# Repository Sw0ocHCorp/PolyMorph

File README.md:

# PolyMorph

> **Documentation** — architecture, mathematics and control pipelines: see [`docs/`](docs/README.md).
> Read it with `cd docs && npm install && npm run start` (Node.js ≥ 20). Every commit is described in [`CHANGELOG.md`](CHANGELOG.md).

PolyMorph is an Open Source Robotic Rust ecosystem.
It is composed of:
* Remote Controller
* Companion Software
* Simulation Flight Controller Software using Godot as Physics Engine

For the begining of the project I build my own encoding system for the communication between all the softwares:

The SOF of ALL the Frames is "abcd"

## FEATURE DATA ID
| Data Label                    | Data ID   | Data                                          |
| :-------------:               | :-------: | :-------------:                               |
| Command                       | 0001      | Single value (Arm `0a` DisArm `0f`)           |
| Teleoperation                 | 0002      | Single value (Arm `0a` DisArm `0f`)           |
| GNSS Positioning              | 0003      | Single value (Arm `0a` DisArm `0f`)           |
| Internal Perception           | 0004      | Single value (Arm `0a` DisArm `0f`)           |
| Lidar Scan                    | 0005      | Single value (Arm `0a` DisArm `0f`)           |
| Camera Vision                 | 0006      | Single value (Arm `0a` DisArm `0f`)           |
Thoses are the IDs of a data chunk. 
A Data chunk is a collection of potentials measurement, data, etc... relative to a feature

## Teleoperation Data ID
| Data Label                    | Data ID   | Data                                          |
| :-------------:               | :-------: | :-------------:                               |
| Arming/Disarm                 | 000a      | Single value (Arm `0a` DisArm `0f`)           |
| Joystick                      | 000b      | 1 Value / Axis (2 Joystick, 4 Axis)           |

## GNSS Positioning Data ID
| Data Label                    | Data ID   | Data                                          |
| :-------------:               | :-------: | :-------------:                               |
| GPS Lat/Lon Mesurement        | 0012      | Lat/Lon/                                      |
| GPS Speed Heading Mesurement  | 0013      | Speed()/Heading()                             |
| Lidar Measurements            | 0014      | Specific Frame with the LiDAR data            |

## Internal Perception Data ID
| Data Label                    | Data ID   | Data                                          |
| :-------------:               | :-------: | :-------------:                               |
| Drone Speed Setpoint          | 000c      | 1 Value / Axis (3D Vector)                    |
| Drone Angles Setpoint         | 000d      | For the begining 1 Value                      |
| Servos Angles Setpoint        | 000e      | 1 Value / Servos                              |
| Drone Speed Mesurement        | 000f      | 1 Value Axis (Sensor Fusion, 2 IMUs: 3 Axis)  |
| Drone Gyro Mesurement         | 0010      | 1 Value Axis (Sensor Fusion, 2 IMUs: 3 Axis)  |
| Altitude Mesurement           | 0011      | 1 Value (Sensor Fusion, 2 Barometers: 1 Value)|
| Battery Mesurement            | 0015      | 1 Value (Remain Energy)                       |

### Lidar Specific Frame
| Data Label                    | Data ID   | Data                                                  |
| :-------------:               | :-------: | :-------------:                                       |
| Lidar measurements range      | 000a      | 2 angles representing the angle range of the lidar    |
| Lidar measurements            | 000b      | LiDAR measurements (distance sensor <-> object)       |

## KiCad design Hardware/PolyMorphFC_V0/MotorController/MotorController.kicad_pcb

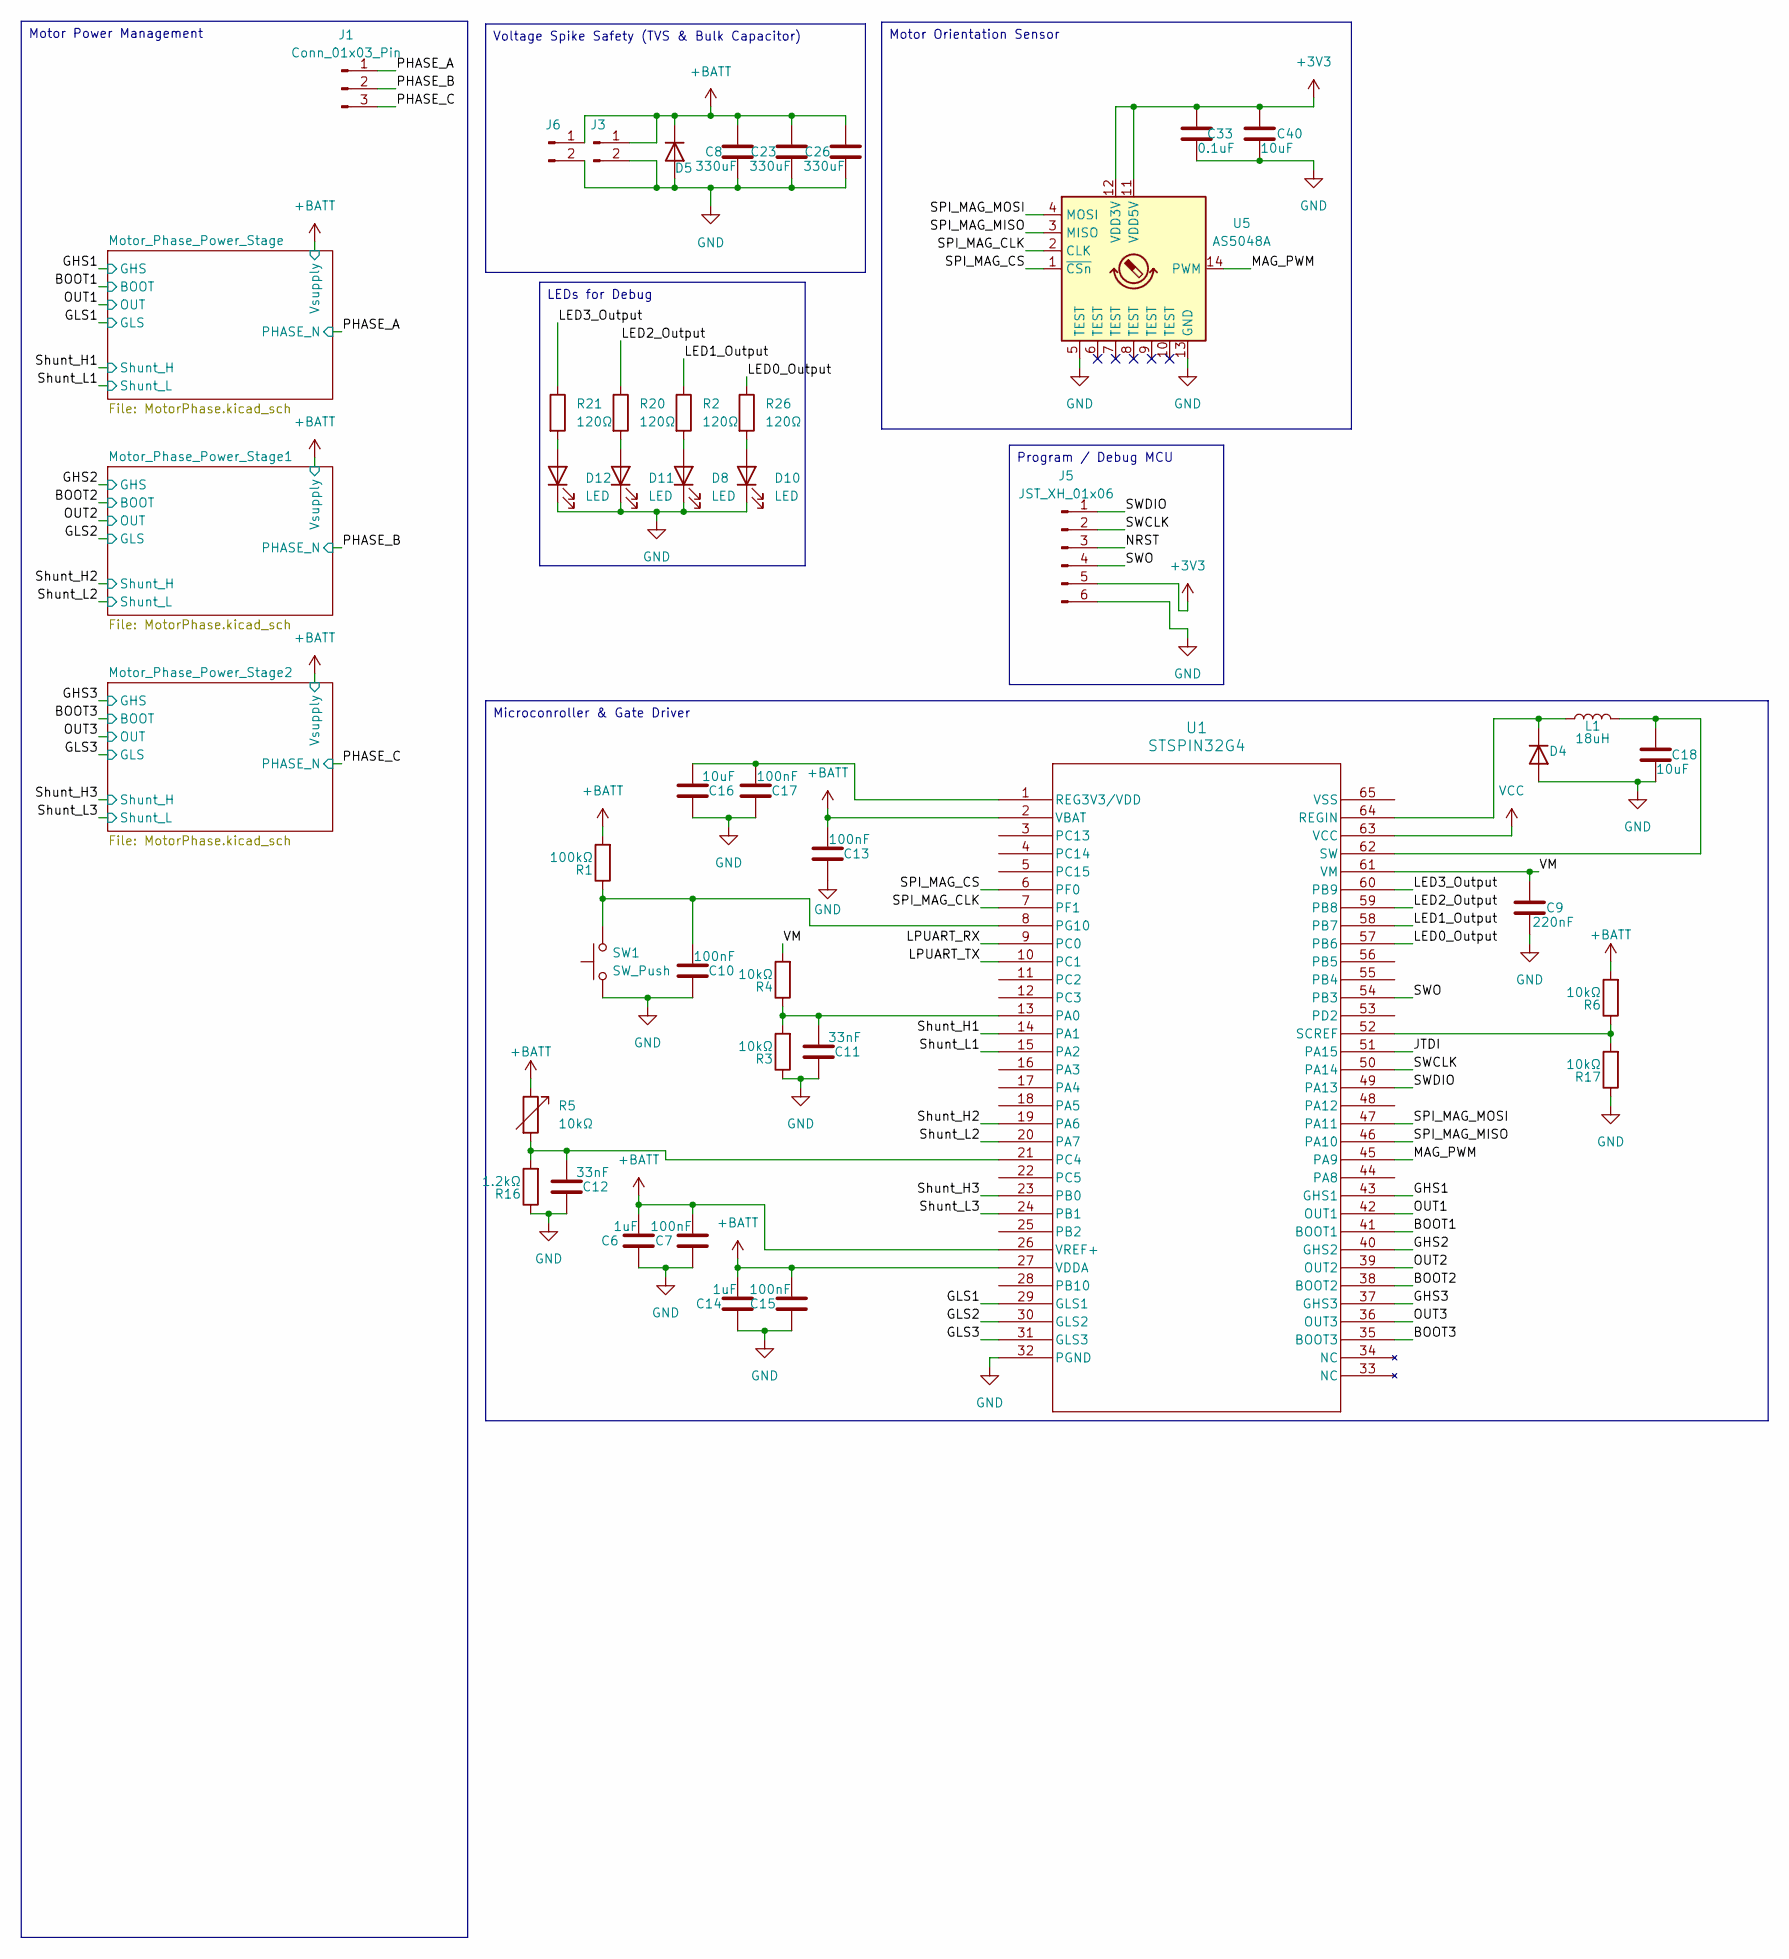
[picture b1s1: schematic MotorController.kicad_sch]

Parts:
C6, C14: 1uF; C_0402_1005Metric
C7, C10, C13, C15, C17: 100nF; C_0402_1005Metric
C8, C23, C26: 330uF; C_Elec_10x10.2
C9: 220nF; C_0402_1005Metric
C11, C12: 33nF; C_0402_1005Metric
C16, C18: 10uF; C_0402_1005Metric
C33: 0.1uF; C_0402_1005Metric
C40: 10uF; C_1206_3216Metric
D4: D_2010_5025Metric
D5: D_SOD-123F
D8, D10, D11, D12: LED; LED_0603_1608Metric
J1: Conn_01x03_Pin; MR60PW
J3: Conn_01x02_Pin; AMASS_XT60-F_1x02_P7.20mm_Vertical
J5: JST_XH_01x06; JST_XH_S6B-XH-SM4-TB_1x06-1MP_P2.50mm_Horizontal
J6: Conn_01x02_Pin; AMASS_XT60PW-M_1x02_P7.20mm_Horizontal
L1: 18uH; L_1008_2520Metric
R1: 100kΩ; R_0603_1608Metric
R2, R20, R21, R26: 120Ω; R_0402_1005Metric
R3, R4, R6, R17: 10kΩ; R_0603_1608Metric
R5: 10kΩ; R_0402_1005Metric
R16: 1.2kΩ; R_0402_1005Metric
SW1: SW_Push; SW_Push_1TS009xxxx-xxxx-xxxx_6x6x5mm
U1: STSPIN32G4; QFN_IN32G4_STM
U5: AS5048A; TSSOP-14_4.4x5mm_P0.65mm

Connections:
+3V3: C33.1, C40.1, J5.5, U5.11 (VDD5V), U5.12 (VDD3V)
+BATT: C6.2, C7.2, C8.2, C13.2, C14.2, C15.2, C23.2, C26.2, D5.1 (K), J3.1, J6.1, R1.2, R5.1, R6.2, U1.2 (VBAT), U1.26 (VREF+), U1.27 (VDDA); also elsewhere on the board
/BOOT1: U1.41 (BOOT1); also elsewhere on the board
/BOOT2: U1.38 (BOOT2); also elsewhere on the board
/BOOT3: U1.35 (BOOT3); also elsewhere on the board
/GHS1: U1.43 (GHS1); also elsewhere on the board
/GHS2: U1.40 (GHS2); also elsewhere on the board
/GHS3: U1.37 (GHS3); also elsewhere on the board
/GLS1: U1.29 (GLS1); also elsewhere on the board
/GLS2: U1.30 (GLS2); also elsewhere on the board
/GLS3: U1.31 (GLS3); also elsewhere on the board
/JTDI: U1.51 (PA15)
/LED0_Output: R26.1, U1.57 (PB6)
/LED1_Output: R2.1, U1.58 (PB7)
/LED2_Output: R20.1, U1.59 (PB8)
/LED3_Output: R21.1, U1.60 (PB9)
/LPUART_RX: U1.9 (PC0)
/LPUART_TX: U1.10 (PC1)
/MAG_PWM: U1.45 (PA9), U5.14 (PWM)
/NRST: J5.3
/OUT1: U1.42 (OUT1); also elsewhere on the board
/OUT2: U1.39 (OUT2); also elsewhere on the board
/OUT3: U1.36 (OUT3); also elsewhere on the board
/PHASE_A: J1.1
/PHASE_B: J1.2
/PHASE_C: J1.3
/SPI_MAG_CLK: U1.7 (PF1), U5.2 (CLK)
/SPI_MAG_CS: U1.6 (PF0), U5.1 (~CSn)
/SPI_MAG_MISO: U1.46 (PA10), U5.3 (MISO)
/SPI_MAG_MOSI: U1.47 (PA11), U5.4 (MOSI)
/SWCLK: J5.2, U1.50 (PA14)
/SWDIO: J5.1, U1.49 (PA13)
/SWO: J5.4, U1.54 (PB3)
/Shunt_H1: U1.14 (PA1); also elsewhere on the board
/Shunt_H2: U1.19 (PA6); also elsewhere on the board
/Shunt_H3: U1.23 (PB0); also elsewhere on the board
/VM: C9.2, R4.2, U1.61 (VM)
GND: C6.1, C7.1, C8.1, C9.1, C10.1, C11.1, C12.1, C13.1, C14.1, C15.1, C16.1, C17.1, C18.1, C23.1, C26.1, C33.2, C40.2, D4.2 (A), D5.2 (A), D8.1 (K), D10.1 (K), D11.1 (K), D12.1 (K), J3.2, J5.6, J6.2, R3.1, R16.1, R17.1, SW1.1, U1.15 (PA2), U1.20 (PA7), U1.24 (PB1), U1.32 (PGND), U5.5 (TEST), U5.13 (GND); also elsewhere on the board
unnamed: D4.1 (K), L1.1, U1.64 (REGIN)
unnamed: D8.2 (A), R2.2
unnamed: D10.2 (A), R26.2
unnamed: D11.2 (A), R20.2
unnamed: D12.2 (A), R21.2
unnamed: C11.2, R3.2, R4.1, U1.13 (PA0)
unnamed: C12.2, R5.2, R16.2, U1.21 (PC4)
unnamed: C10.2, R1.1, SW1.2, U1.8 (PG10)
unnamed: C16.2, C17.2, U1.1 (REG3V3/VDD)
unnamed: R6.1, R17.2, U1.52 (SCREF)
unnamed: C18.2, L1.2, U1.62 (SW)
VCC: U1.63 (VCC)

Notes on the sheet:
LEDs for Debug
Motor Orientation Sensor
Microconroller & Gate Driver
Motor Power Management
Program / Debug MCU
Voltage Spike Safety (TVS & Bulk Capacitor)

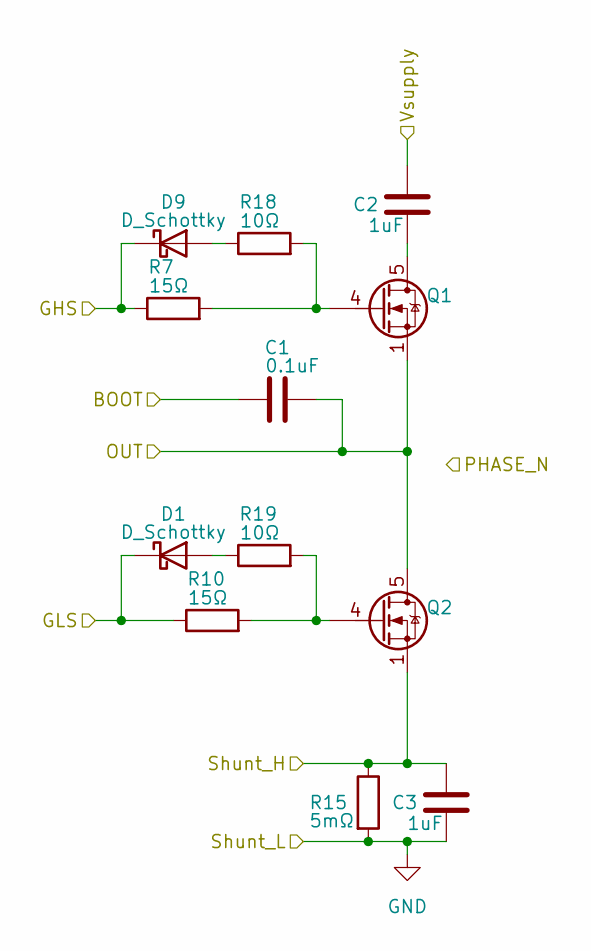
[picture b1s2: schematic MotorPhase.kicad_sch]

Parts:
C1: 0.1uF; C_0402_1005Metric
C2, C3: 1uF; C_0402_1005Metric
D1, D9: D_Schottky; D_SOD-123F
Q1, Q2: BSC016N06NS; Infineon_PG-TDSON-8_6.15x5.15mm
R7, R10: 15Ω; R_0402_1005Metric
R15: 5mΩ; R_4527_11375MetricL
R18, R19: 10Ω; R_0402_1005Metric

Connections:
+BATT: C2.2; also elsewhere on the board
/BOOT1: C1.1; also elsewhere on the board
/GHS1: D9.1 (K), R7.1; also elsewhere on the board
/GLS1: D1.1 (K), R10.1; also elsewhere on the board
/OUT1: C1.2, Q1.1 (S), Q1.2 (S), Q1.3 (S), Q2.5 (D); also elsewhere on the board
/Shunt_H1: C3.2, Q2.1 (S), Q2.2 (S), Q2.3 (S), R15.1; also elsewhere on the board
GND: C3.1, R15.2; also elsewhere on the board
unnamed: D1.2 (A), R19.1
unnamed: D9.2 (A), R18.1
unnamed: C2.1, Q1.5 (D)
unnamed: Q1.4 (G), R7.2, R18.2
unnamed: Q2.4 (G), R10.2, R19.2

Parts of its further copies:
C4, C20: 0.1uF; C_0402_1005Metric
C5, C19, C21, C22: 1uF; C_0402_1005Metric
D2, D3, D6, D7: D_Schottky; D_SOD-123F
Q3, Q4, Q5, Q6: BSC016N06NS; Infineon_PG-TDSON-8_6.15x5.15mm
R8, R9, R14, R22: 15Ω; R_0402_1005Metric
R11, R12, R23, R24: 10Ω; R_0402_1005Metric
R13, R25: 5mΩ; R_4527_11375MetricL

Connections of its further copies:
+BATT: C5.2, C21.2; also elsewhere on the board
/BOOT2: C4.1; also elsewhere on the board
/BOOT3: C20.1; also elsewhere on the board
/GHS2: D2.1 (K), R8.1; also elsewhere on the board
/GHS3: D6.1 (K), R14.1; also elsewhere on the board
/GLS2: D3.1 (K), R9.1; also elsewhere on the board
/GLS3: D7.1 (K), R22.1; also elsewhere on the board
/OUT2: C4.2, Q3.1 (S), Q3.2 (S), Q3.3 (S), Q4.5 (D); also elsewhere on the board
/OUT3: C20.2, Q5.1 (S), Q5.2 (S), Q5.3 (S), Q6.5 (D); also elsewhere on the board
/Shunt_H2: C19.2, Q4.1 (S), Q4.2 (S), Q4.3 (S), R13.1; also elsewhere on the board
/Shunt_H3: C22.2, Q6.1 (S), Q6.2 (S), Q6.3 (S), R25.1; also elsewhere on the board
GND: C19.1, C22.1, R13.2, R25.2; also elsewhere on the board
unnamed: D2.2 (A), R11.1
unnamed: D3.2 (A), R12.1
unnamed: D6.2 (A), R23.1
unnamed: D7.2 (A), R24.1
unnamed: C5.1, Q3.5 (D)
unnamed: Q3.4 (G), R8.2, R11.2
unnamed: Q4.4 (G), R9.2, R12.2
unnamed: C21.1, Q5.5 (D)
unnamed: Q5.4 (G), R14.2, R23.2
unnamed: Q6.4 (G), R22.2, R24.2

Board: 2 copper layers, 78 parts (5 on the bottom side), 57 nets, no tracks yet.

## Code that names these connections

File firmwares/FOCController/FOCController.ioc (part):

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Mcu.Name=STM32G431V(6-8-B)Tx
Mcu.Package=LQFP100
Mcu.UserName=STM32G431VBTx
PA0.GPIOParameters=GPIO_Label
PA0.GPIO_Label=ADC1_Bus_Volt_Monitor
PA0.Mode=IN1-Single-Ended
PA0.Signal=ADC1_IN1
PA1.Mode=Standalone
PA1.Signal=OPAMP1_VINP
PA10.Mode=Full_Duplex_Master
PA10.Signal=SPI2_MISO
PA11.Mode=Full_Duplex_Master
PA11.Signal=SPI2_MOSI
PA13.Mode=JTAG_4_pins
PA13.Signal=SYS_JTMS-SWDIO
PA14.Mode=JTAG_4_pins
PA14.Signal=SYS_JTCK-SWCLK
PA15.Mode=JTAG_4_pins
PA15.Signal=SYS_JTDI
PA2.Mode=Standalone
PA2.Signal=OPAMP1_VOUT
PA3.Mode=Standalone
PA3.Signal=OPAMP1_VINM
PA5.Mode=Standalone
PA5.Signal=OPAMP2_VINM
PA6.Mode=Standalone
PA6.Signal=OPAMP2_VOUT
PA7.Mode=Standalone
PA7.Signal=OPAMP2_VINP
PA9.Signal=S_TIM2_CH3
PB0.Mode=Standalone
PB0.Signal=OPAMP3_VINP
PB1.Mode=Standalone
PB1.Signal=OPAMP3_VOUT
PB2.Mode=Standalone
PB2.Signal=OPAMP3_VINM
PB3.Mode=JTAG_4_pins
PB3.Signal=SYS_JTDO-SWO
PB6.GPIOParameters=GPIO_Label
PB6.GPIO_Label=LED0_Output
PB6.Signal=GPIO_Output
PB7.GPIOParameters=GPIO_Label
PB7.GPIO_Label=LED1_Output
PB7.Signal=GPIO_Output
PB8-BOOT0.GPIOParameters=GPIO_Label
PB8-BOOT0.GPIO_Label=LED2_Output
PB8-BOOT0.Signal=GPIO_Output
PB9.GPIOParameters=GPIO_Label
PB9.GPIO_Label=LED3_Output
PB9.Signal=GPIO_Output
PC0.Mode=Asynchronous
PC0.Signal=LPUART1_RX
PC1.Mode=Asynchronous
PC1.Signal=LPUART1_TX
PC4.GPIOParameters=GPIO_Label
PC4.GPIO_Label=ADC2_Temp_Monitor
PC4.Mode=IN5-Single-Ended
PC4.Signal=ADC2_IN5
PC8.Mode=I2C
PC8.Signal=I2C3_SCL
PC9.Mode=I2C
PC9.Signal=I2C3_SDA
PE10.Mode=PWM Generation2 CH2 CH2N
PE10.Signal=TIM1_CH2N
PE11.Signal=S_TIM1_CH2
PE12.Mode=PWM Generation3 CH3 CH3N
PE12.Signal=TIM1_CH3N
PE13.Signal=S_TIM1_CH3
PE14.Mode=Activate-Break-Input-2
PE14.Signal=TIM1_BKIN2
PE15.Mode=Activate-Break-Input
PE15.Signal=TIM1_BKIN
PE7.GPIOParameters=GPIO_Label
PE7.GPIO_Label=WAKE
PE7.Signal=GPIO_Output
PE8.Mode=PWM Generation1 CH1 CH1N
PE8.Signal=TIM1_CH1N
PE9.Signal=S_TIM1_CH1
PF0-OSC_IN.Signal=SPI2_NSS
PF1-OSC_OUT.Mode=Full_Duplex_Master
PF1-OSC_OUT.Signal=SPI2_SCK
PG10-NRST.GPIOParameters=GPIO_Label
PG10-NRST.GPIO_Label=RESET_Input
PG10-NRST.Signal=GPIO_Input
RCC.HSE_VALUE=8000000
RCC.SYSCLKFreq_VALUE=16000000
board=custom

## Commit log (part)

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2025-11-15 SLAM & CAM scene Ready
2025-11-15 Setup project
2025-11-20 Setup projet for RUST
2025-11-23 Communication between Companion and Godot Flight Controller OK
    - godot.flight_controller:
    + UDPChannel= Sequential, not in dedicated thread because Multithread issues in GODOT
    - companion:
    + UDPChannel= In dedicated thread
2025-11-26 Channel and Module / Worker code sanitation in Companion project
    - Sanitation to implement new futures features more easily:
    + A Module is a struct containing a Module Linker in its variables to create execution graph with multiple modules and execute tasks in sequences.
    + A Process is a trait giving the ability to execute a task
    + A Worker is a struct executing the task of another struct implementing Process in a dedicated thread
    + A worker factory is a struct creating Worker based on object implementing process trait to manage the life cycle of the process structs workers
    + A Channel is the base class for all the communication channels (UART, I2C, UDP, ...).
2025-11-26 Creation of a RoboMorph library
    - The robomorph library is a project library would contains the generic code common to the different projects (flight_controller, companion, remote controller)
2025-11-26 Setup robomorph lib import for polymorph and companion projects
2025-11-27 LiDAR implementation OK
    - Using software RayCast:
    + POC
2025-11-28 Lidar measure sequence in right order
    - Lidar measurements are well organize
    + like rotating scan ( always from right to left or in the reverse order)
2025-11-30 Controller GUI with Factory to run Worker threads
    - Simple Iced GUI:
    + Controller is just(for now) a simple Iced GUI to build the Controller software pipeline
    - Factory in Iced Application:
    + The Factory run all the workers when the window is opened
    + The factory end all the threads when the window is closed
2025-12-04 Com UDP AutonomyNode => Controller Slint Application OK
    - AutonomyNode:
    + Extending the Observer to be able to put event data in observer buffer
    The Module can get the observer buffer data at a different frequency than the event put data into
    + UDPChannel can be used outside a work (Sequentially)
    - Controller:
    + Using Slint as GUI library
2025-12-09 POC Serialization / Deserialization System OK
    - Translator:
    Object to translate an incoming frame(Vec<u8>) to a list of structs messages
    - Translatable:
    Trait for object that can be represent as a struct to be processed by the robot or as a frame to be sent through UDP, UART, etc...
    - FeatureMessage:
    Enum to track the different types of message that can be processed / transmit
2025-12-15 Project Rework
2025-12-18 Workers, communication between them and UDP interface OK
    - Event / Observer:
    + Objects used to create relations between objects, modules, etc...
    synchronously or asynchronously(with a queue)
    - Module:
    + A trait to define the main task of an object
    - Worker:
2025-12-21 Serialization / Deserialization OK
    - POC OK with LidarMeasurements
    - Translatable:
    + Trait that model data structures / message that can be convert to bytes chunk to build frame and that can fill its fields from a frame
2025-12-22 Worker Factory V0 OK
    - Creation of Workers(synchrone / Asynchrone) based on modules
    - Model execution graphs by linking workers together
    - Start specific workers (synchronous/asynchronous)
2025-12-23 Lidar Data Visualization Pipeline OK
2025-12-28 POC Lidar Scan OK
2025-12-29 Lidar angles express in relative frame
2025-12-31 Lidar Obstacle Segmentation OK
    - Segmentation Algorithm:
    + DBSCAN like algorithm
2026-01-07 POC Mahony Filter OK And Code organized in packages
    - UDPChannel:
    + Using SocketRef to configure the MAX_RECEPTION_BUFFER size on UDP connections (to be sure the LiDAR scan data can be received without problems)
    - package filtering:
    + MahonyFilter= Implementation of the first Pose estimation filter (only orientation), needs to be tuned to increase estimation accuracy
    - package pose:
    + IMUData=
2026-01-08 Mahony filter Tuned
    /!\ Kd not 0.0 because big Kp cause oscillation on pitch and roll estimation
    - Orientation estimation converge well
    - Test with no noise on Magnetic field and angular velocity (gyrometer)
2026-01-15 POC Dummy Lidar Object Mapping OK
    - Frequencies modifications:
    + UDPChannel Worker's frequency is changed for -1 -> Udp channel put every UDP frame in other modules buffer when they are received.
    Avoid latency in UDP frame reception
    + Frequency of UDP Channel in Autonomy node is set to 60Hz because GODOT simulation run in 120Hz and its frequency can't be changed
    - Dummy Lidar Object Mapping:
    + Using Robot Pose to put the scaned object in the World Frame.
2026-02-09 UKF not works, it needs to be tuned
2026-02-10 Building file logger
2026-02-12 UKF estimation drifting if gyro measurements != 0
    Fix error in IMU measurements generation
2026-02-13 Add visualization dashboard
    Fix some frame orientation errors
2026-02-14 UKF OK
    Validated on Godot Simulation
2026-02-14 UKF for orientation estimation OK
    /!\ Works only for system without translations (with fixed location)
    Validated on Godot Simulation
2026-02-15 Comments in the UKF implementations
2026-02-16 Setup Osprey Bicopter asset
2026-02-17 Bicopter wing rotating OK
    Just rotating Arm of the wing by pushing Y button
2026-02-23 Control the orientation of the wings OK
2026-02-25 Setup Bicopter control pipeline
2026-02-26 Balancing wings of the drone
2026-02-26 Add Hardware board project
2026-03-05 FOC Controller Board Schematic OK
2026-03-06 Flashing Board and Embassy setup OK
2026-03-12 Event - Observer sync system OK
    - A bit different from the system using std (in the base lib: robomorph)
    Observer struct being replace with a trait, Worker implement itself this trait
    - Using lifetime statement to tell to the compiler that all objects linked to the Event-Observer system live long enough to maintain it.
    No usage of unsafe operations to stay in RUST context and let to the borrow checker & ownership system the management of the memory
2026-03-19 Rework of Event - Observer system according rust constraints
    - min time between 2 worker tasks executions ( 3ms > x > 2ms)
    - Using orchestrator to manage the event data publication
    - Using queue to pass callbacks data to the modules
2026-04-09 Schematic OK & Setup FOC Controller board firmware using STM IDE (C / C++)
    - Using RUST for Low Level firmware creates a lot of software archiecture constraints not compatible with ergonomic system - A rework in Rust could be considered in the future
2026-04-09 Footprint placements and screens
2026-05-23 Base firmware architecture OK
    Publisher / Observers system:
    - Publisher put a given data(structure or classic type) in a pipeline
    - Observers can connect themself to one or many pipelines that match it's data struct or type
    - Observers received the data from the pipeline and can execute callback function that use this data
    Workers are like nodes in ROS:
    - Can execute a specific task at a given frequency
2026-06-06 Setup Gazebo environment OK
    - Vehicles: Folder that contains the vehicle models files
    + Osprai:
    * Bicopter drone with
    2 Arms
    2 Propellers
    1 Lidar
2026-06-07 Asserv arm orientation OK
2026-06-26 New Publisher / Observer architecture removing almost all Arc<Mutex>
    - Remove all the unused folders
    - Scheduler:
    + Object that can create(and own) / run / run in dedicated threads / stop processes chains
    + The scheduler contains(and own) also hardware interfaces that can give the ability to communicate with hardware devices or external endpoints
    - Process:
    + Processes chains are object that contains (and own) processes and can run processes main tasks one after another
2026-06-26 Auto stash before merge of "Total_Rework" and "main"
